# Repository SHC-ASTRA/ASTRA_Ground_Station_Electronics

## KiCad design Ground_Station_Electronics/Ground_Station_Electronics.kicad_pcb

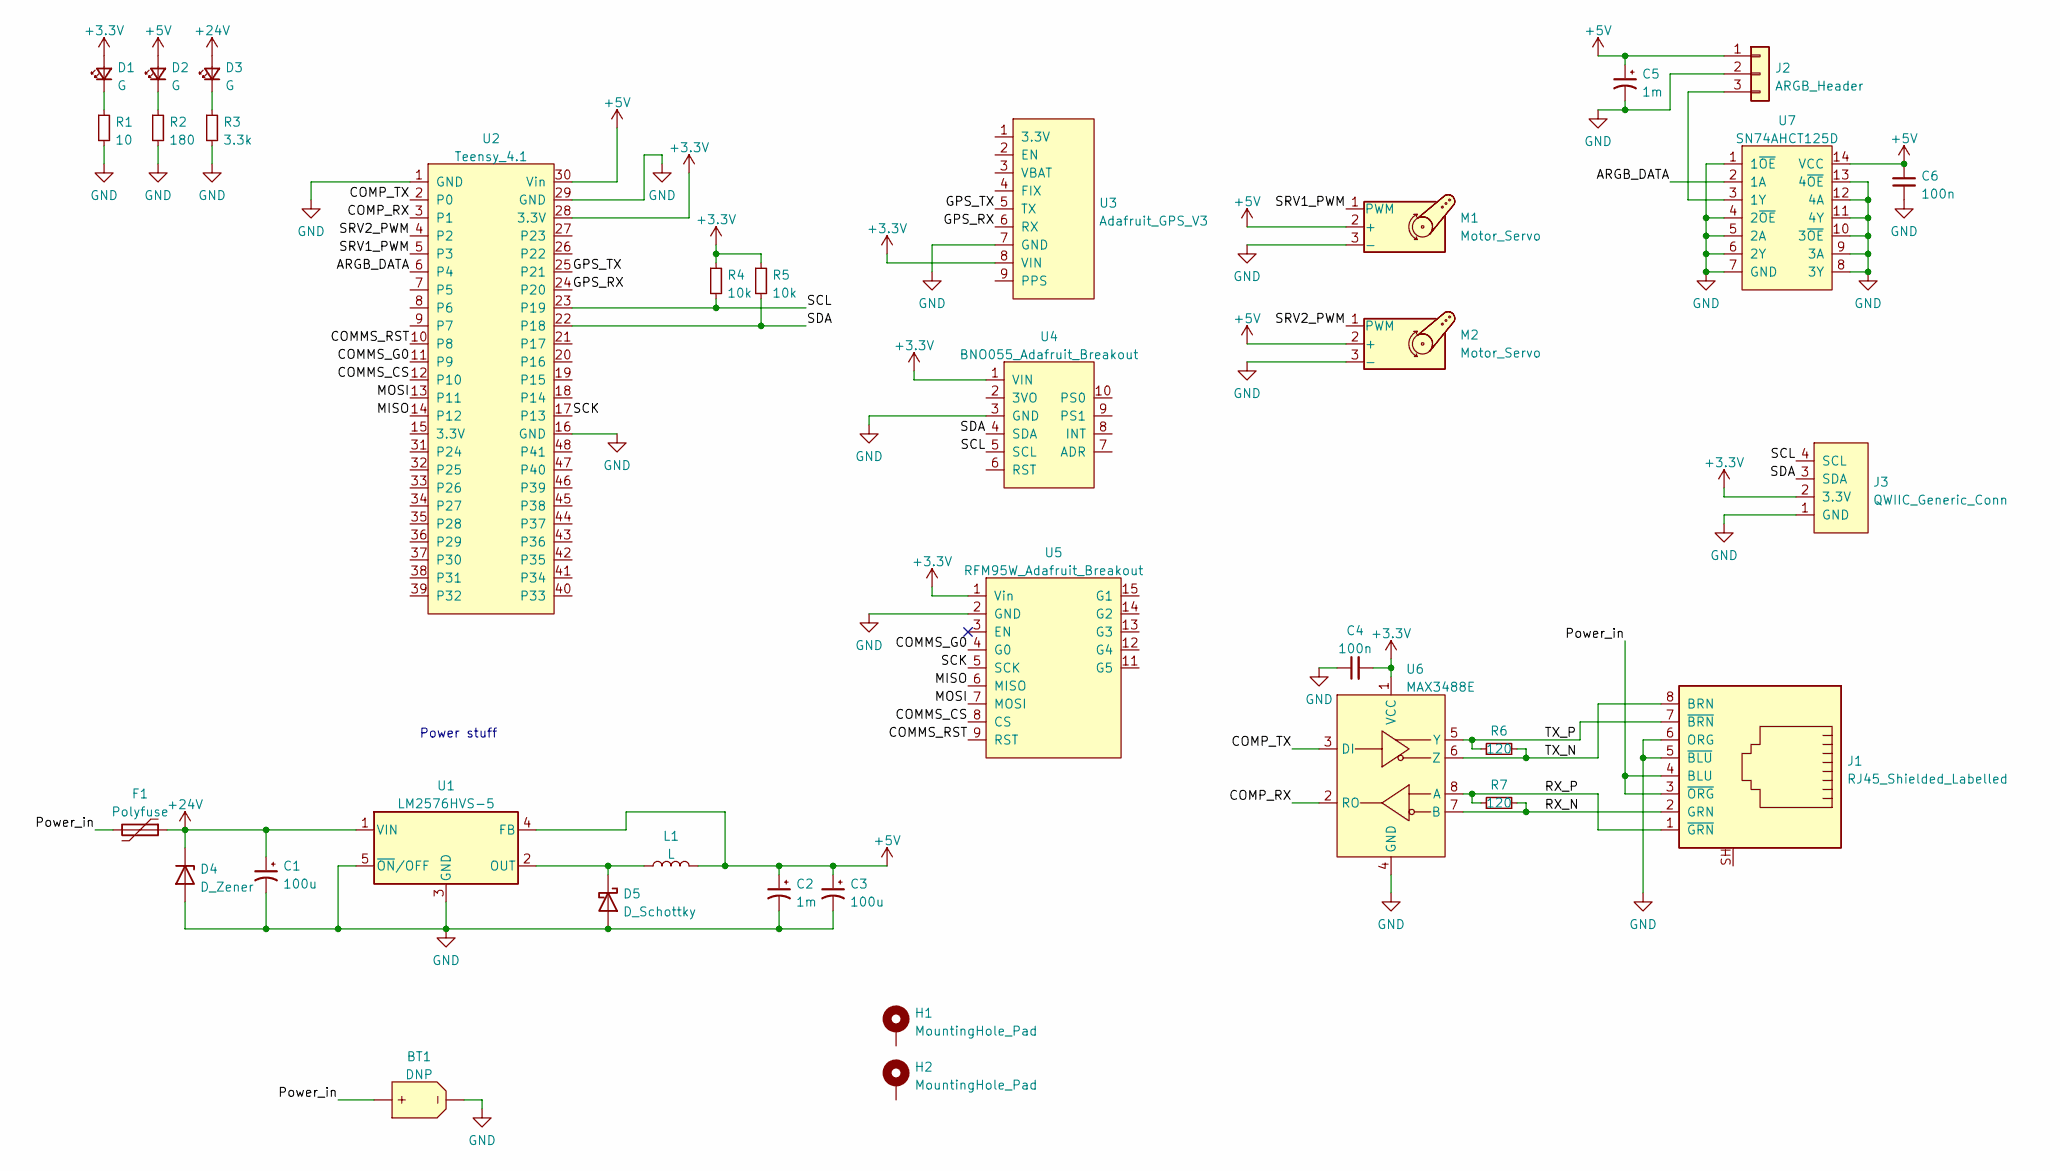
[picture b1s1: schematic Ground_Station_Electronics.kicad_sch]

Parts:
BT1: DNP; AMASS_XT30U-M_1x02_P5.0mm_Vertical
C1, C3: 100u; CP_Elec_10x10; Digikey Part Num 50PEV100M10X10.5CT-ND
C2, C5: 1m; C_Radial_D10.0mm_H12.5mm_P5.00mm; Digikey Part Num P16300-ND
C4, C6: 100n; C_0603_1608Metric
D1, D2, D3: G; LED_0603_1608Metric_Pad1.05x0.95mm_HandSolder; Digikey Part Num 732-4971-1-ND
D4: D_Zener; D_SMB_Handsoldering; Digikey Part Num 1655-SMBJ36ACT-ND
D5: D_Schottky; D_SMC_Handsoldering; Digikey Part Num B560C-FDICT-ND
F1: Polyfuse; Fuse_2920_7451Metric_Pad2.10x5.45mm_HandSolder; Digikey Part Num 507-1747-1-ND
H1, H2: MountingHole_Pad; MountingHole_4.3mm_M4_Pad
J1: RJ45_Shielded_Labelled; RJ45_Amphenol_RJHSE5380; Digikey Part Num RJHSE5E80-ND
J2: ARGB_Header; JST_PH_B3B-PH-K_1x03_P2.00mm_Vertical
J3: QWIIC_Generic_Conn; JST_SH_BM04B-SRSS-TB_1x04-1MP_P1.00mm_Vertical
L1: L; L_Wuerth_HCF-2920; Digikey Part Num 732-11715-ND
M1, M2: Motor_Servo; PinHeader_1x03_P2.54mm_Vertical
R1: 10; R_0603_1608Metric; Digikey Part Num 311-10.0HRCT-ND
R2: 180; R_0603_1608Metric; Digikey Part Num 311-180HRCT-ND
R3: 3.3k; R_0603_1608Metric; Digikey Part Num 311-3.30KHRCT-ND
R4, R5: 10k; R_0603_1608Metric
R6, R7: 120; R_0603_1608Metric; Digikey Part Num RMCF0603FT120RCT-ND
U1: LM2576HVS-5; TO-263-5_TabPin3; Digikey Part Num LM2576HVS-5.0/NOPB-ND
U2: Teensy_4.1; Teensy4.1; Digikey Part Num 1568-DEV-16996-ND
U3: Adafruit_GPS_V3; Adafruit_GPS_Breakout; Digikey Part Num 1528-1153-ND
U4: BNO055_Adafruit_Breakout; Adafruit_BNO055; Digikey Part Num 1528-4646-ND
U5: RFM95W_Adafruit_Breakout; Adafruit_RFM95W; Digikey Part Num 1528-1667-ND
U6: MAX3488E; SOIC-8_3.9x4.9mm_P1.27mm; Digikey Part Num MAX3488EESA+TCT-ND
U7: SN74AHCT125D; SOIC-14_3.9x8.7mm_P1.27mm; Digikey Part Num 296-4652-5-ND

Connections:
+3V3: C4.2, D1.2 (A), J3.2 (3.3V), R4.1, R5.1, U2.28 (3.3V), U3.8 (VIN), U4.1 (VIN), U5.1 (Vin), U6.1 (VCC)
+5V: C2.1, C3.1, C5.1, C6.2, D2.2 (A), J2.1, L1.2, M1.2 (+), M2.2 (+), U1.4 (FB), U2.30 (Vin), U7.14 (VCC)
+24V: C1.1, D3.2 (A), D4.1 (K), F1.1, U1.1 (VIN)
/ARGB_DATA: U2.6 (P4), U7.2 (1A)
/COMMS_CS: U2.12 (P10), U5.8 (CS)
/COMMS_G0: U2.11 (P9), U5.4 (G0)
/COMMS_RST: U2.10 (P8), U5.9 (RST)
/COMP_RX: U2.3 (P1), U6.2 (RO)
/COMP_TX: U2.2 (P0), U6.3 (DI)
/GPS_RX: U2.24 (P20), U3.6 (RX)
/GPS_TX: U2.25 (P21), U3.5 (TX)
/MISO: U2.14 (P12), U5.6 (MISO)
/MOSI: U2.13 (P11), U5.7 (MOSI)
/Power_in: BT1.2 (Pos), F1.2, J1.3 (~ORG), J1.4 (BLU)
/RX_N: J1.2 (GRN), R7.2, U6.7 (B)
/RX_P: J1.1 (~GRN), R7.1, U6.8 (A)
/SCK: U2.17 (P13), U5.5 (SCK)
/SCL: J3.4 (SCL), R4.2, U2.23 (P19), U4.5 (SCL)
/SDA: J3.3 (SDA), R5.2, U2.22 (P18), U4.4 (SDA)
/SRV1_PWM: M1.1 (PWM), U2.5 (P3)
/SRV2_PWM: M2.1 (PWM), U2.4 (P2)
/TX_N: J1.8 (BRN), R6.2, U6.6 (Z)
/TX_P: J1.7 (~BRN), R6.1, U6.5 (Y)
GND: BT1.1 (Neg), C1.2, C2.2, C3.2, C4.1, C5.2, C6.1, D4.2 (A), D5.2 (A), J1.5 (~BLU), J1.6 (ORG), J2.2, J3.1 (GND), M1.3 (-), M2.3 (-), R1.2, R2.2, R3.2, U1.3 (GND), U1.5 (~ON/OFF), U2.1 (GND), U2.16 (GND), U2.29 (GND), U3.7 (GND), U4.3 (GND), U5.2 (GND), U6.4 (GND), U7.1 (1~OE), U7.4 (2~OE), U7.5 (2A), U7.6 (2Y), U7.7 (GND), U7.8 (3Y), U7.9 (3A), U7.10 (3~OE), U7.11 (4Y), U7.12 (4A), U7.13 (4~OE)
unnamed: D1.1 (K), R1.1
unnamed: D2.1 (K), R2.1
unnamed: D3.1 (K), R3.1
unnamed: D5.1 (K), L1.1, U1.2 (OUT)
unnamed: J2.3, U7.3 (1Y)

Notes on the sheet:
Power stuff

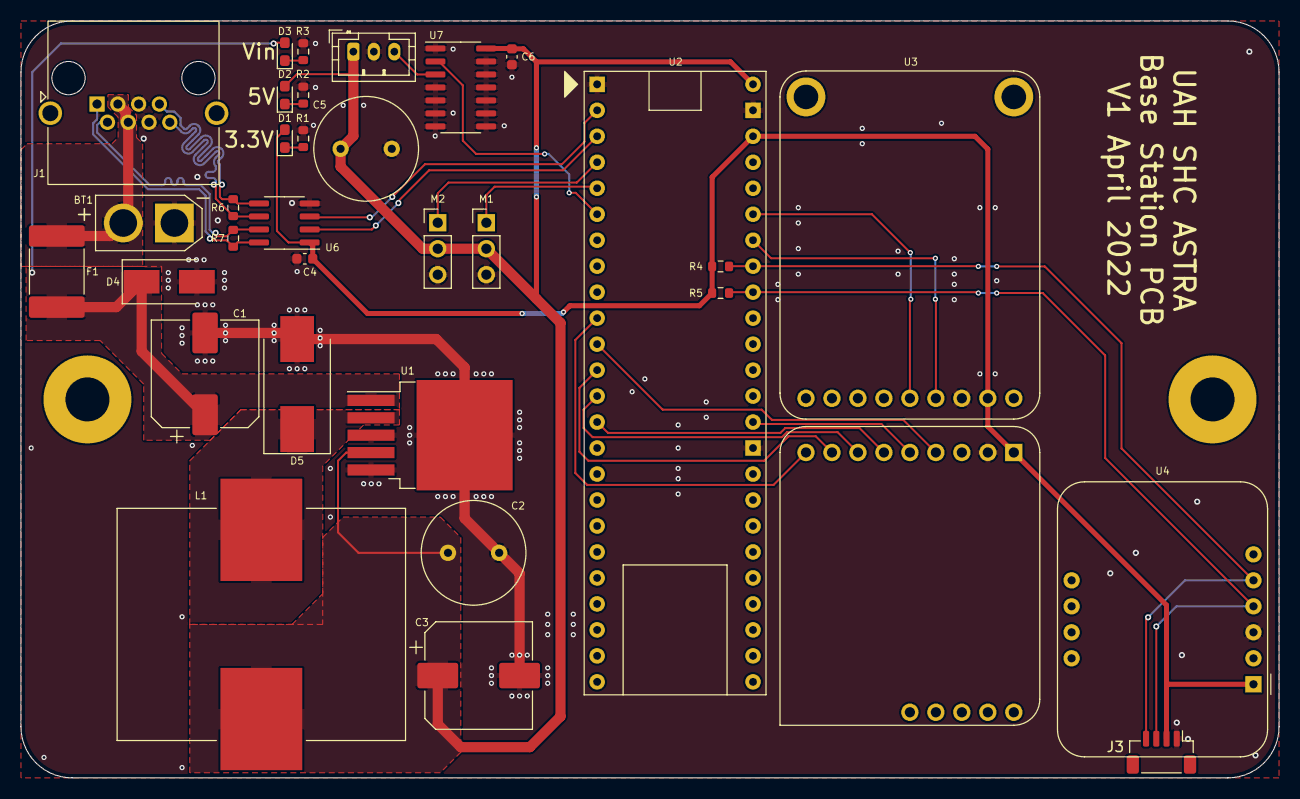
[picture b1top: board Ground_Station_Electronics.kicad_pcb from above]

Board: 2 copper layers, 123.0 x 74.0 mm, 35 parts (0 on the bottom side), 29 nets.

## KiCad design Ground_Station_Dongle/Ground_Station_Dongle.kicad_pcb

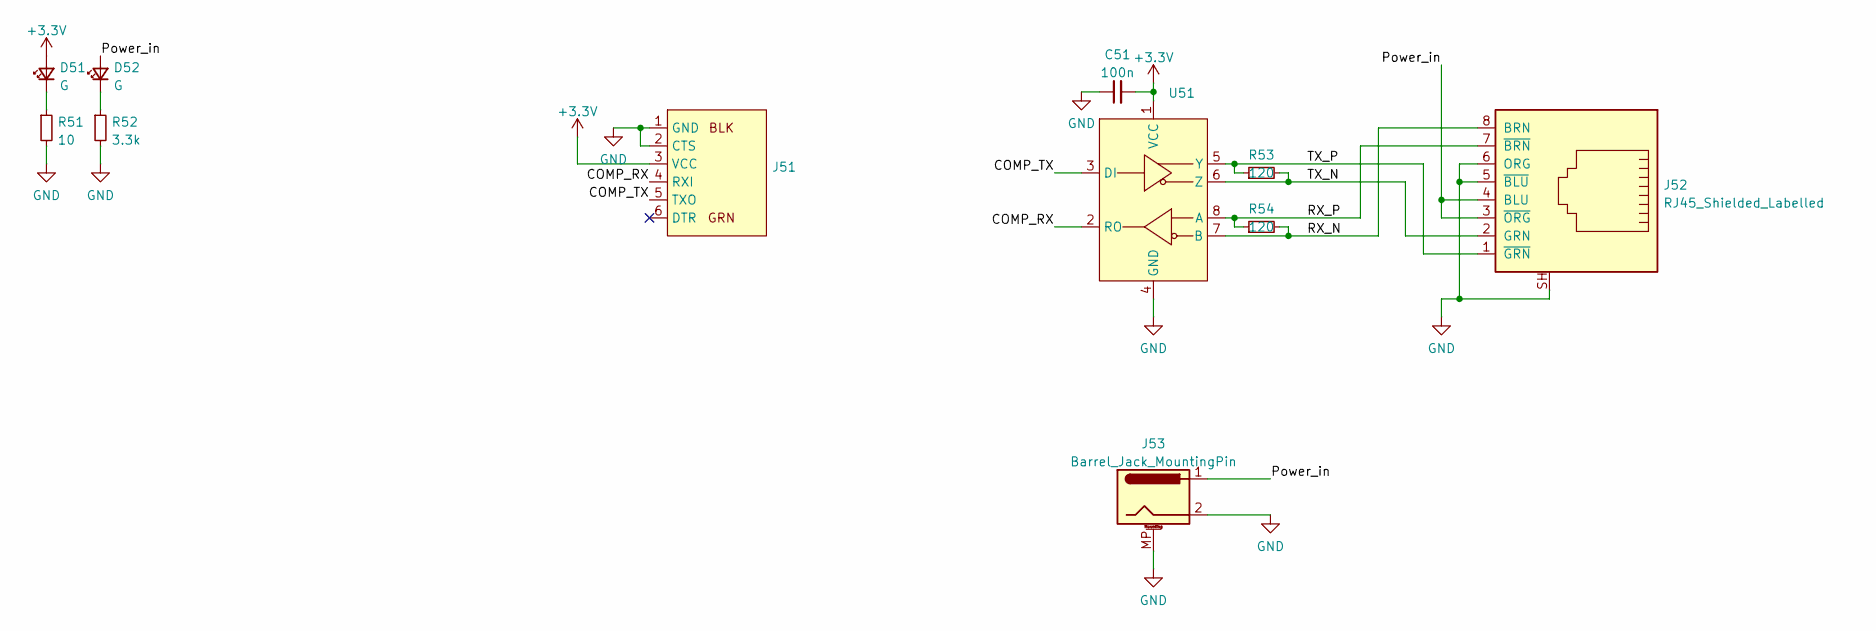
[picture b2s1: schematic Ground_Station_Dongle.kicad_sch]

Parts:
C51: 100n; C_0603_1608Metric
D51, D52: G; LED_0603_1608Metric_Pad1.05x0.95mm_HandSolder; Digikey Part Num 732-4971-1-ND
J51: (no value)
J52: RJ45_Shielded_Labelled; RJ45_Amphenol_RJHSE5380; Digikey Part Num RJHSE5E80-ND
J53: Barrel_Jack_MountingPin; BarrelJack_CUI_PJ-063AH_Horizontal; Digikey Part Num CP-063AH-ND
R51: 10; R_0603_1608Metric; Digikey Part Num 311-10.0HRCT-ND
R52: 3.3k; R_0603_1608Metric; Digikey Part Num 311-3.30KHRCT-ND
R53, R54: 120; R_0603_1608Metric; Digikey Part Num RMCF0603FT120RCT-ND
U51: Digikey Part Num MAX3488EESA+TCT-ND

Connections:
+3V3: C51.2, D51.2 (A), J51.3 (VCC), U51.1 (VCC)
/COMP_RX: J51.4 (RXI), U51.2 (RO)
/COMP_TX: J51.5 (TXO), U51.3 (DI)
/Power_in: D52.2 (A), J52.3 (~ORG), J52.4 (BLU), J53.1
/RX_N: J52.8 (BRN), R54.2, U51.7 (B)
/RX_P: J52.7 (~BRN), R54.1, U51.8 (A)
/TX_N: J52.2 (GRN), R53.2, U51.6 (Z)
/TX_P: J52.1 (~GRN), R53.1, U51.5 (Y)
GND: C51.1, J51.1 (GND), J51.2 (CTS), J52.5 (~BLU), J52.6 (ORG), J52.SH, J53.2, J53.MP (MountPin), R51.2, R52.2, U51.4 (GND)
unnamed: D51.1 (K), R51.1
unnamed: D52.1 (K), R52.1

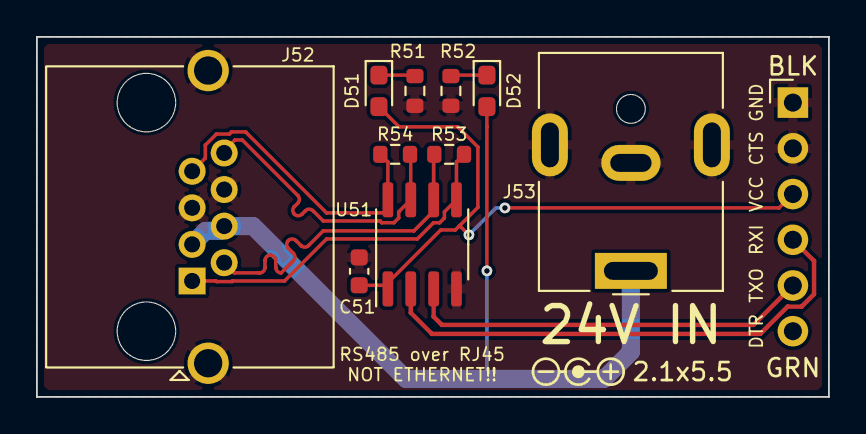
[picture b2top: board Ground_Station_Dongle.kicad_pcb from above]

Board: 2 copper layers, 44.0 x 20.0 mm, 11 parts (0 on the bottom side), 11 nets.

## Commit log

2021-10-23 Added Files
2022-03-26 Started Schematic
    Not completely finished yet but maybe almost
2022-04-02 Upgraded to KiCAD6, restarted to fix file issues
2022-04-02 fixed library
2022-04-02 worked on rs485
2022-04-02 Take 2 Electric Boogaloo
    Migrated to KiCad 6.0. Re-added the schematic stuff from last time in the new version, hopefully with working libraries
2022-04-02 Working on schematic
2022-04-03 worked on schematic and footprints
2022-04-03 should be schematic done?
2022-04-03 started PCB
2022-04-03 Forgot to save schematic
2022-04-03 design rules and grouping
2022-04-03 Layout and routing
2022-04-03 "done" but ugly
2022-04-06 Working on PCB
2022-04-06 schematic save
2022-04-15 exported
2022-04-16 Added Dongle
2022-04-20 Updated, ready to order
